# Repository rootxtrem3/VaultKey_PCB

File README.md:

# VaultKey USB

> **This README is also generated by an AI agent cuz why not. All those PCB designing that i ain't used to and coding are enough for me!**

VaultKey USB is a compact ESP32-S3 hardware-key PCB with a native USB-A edge
connector, 128x64 OLED, four navigation buttons, a recessed reset switch, and a CR2032-backed DS1307 real-time
clock. This project targets **KiCad 10** and includes the routed PCB, matching
schematic, project rules, manufacturing data, assembly data, reports, STEP
model, and documentation plots.

## Validation status

The release artifacts in this directory were generated with KiCad 10.0.8.

| Check | Result |
|---|---:|
| PCB DRC | **0 violations, 0 unconnected pads** |
| PCB pad connectivity | **0 unconnected pads after GND stitching via** |
| Schematic ERC | **0 violations** |
| Schematic-to-PCB comparison | **105 connected pins, 0 mismatches** |
| Board outline | **112.500 x 50.000 mm** |
| Copper layers / thickness | **2 / 1.600 mm** |
| USB D+/D- routed-length mismatch | **6.625 mm** |
| USB-A PCB-edge pad order/geometry | **PASS** |

Rev E adds TP1 BOOT-to-GND recovery pads and MCU GPIO1 control of the green
status LED. Existing component placement and board outline are unchanged. The
current PCB passes DRC after copper-zone refill. Gerbers, drill files, and
fabrication archives are regenerated from this board. Validate the assembled
hardware before production use.

The machine-generated reports are under `fabrication/reports/`.
Cosmetic silkscreen-to-copper, silkscreen-overlap, and silkscreen-edge checks
are intentionally set to ignore in the project rules; electrical, clearance,
hole, courtyard, connectivity, and copper-edge checks remain enabled.

## Mechanical definition

- Overall coordinate bounds: `X=0..112.5 mm`, `Y=0..50.0 mm`.
- Main body: `X=12.0..112.5 mm`, **100.5 x 50.0 mm**.
- USB-A tongue: `X=0..12.0 mm`, `Y=19.0..31.0 mm`, with 0.5 mm 45-degree
  tip chamfers.
- Four 2.7 mm NPTH mounting holes:
  - H1 `(16.0, 3.5)`
  - H2 `(15.0, 47.0)`
  - H3 `(108.5, 3.5)`
  - H4 `(108.0, 46.0)`
- Two-layer, 1.6 mm FR4. All vias are tented on both sides.
- Contact finish: standard ENIG; hard-gold edge plating is not specified for
  this low-cycle prototype. Confirm insertion-cycle requirements with the
  fabricator and USB host connector.
- Front and rear silkscreens include component references; controls and major
  blocks also carry functional labels for assembly and use.

The required USB, display, module, RTC, and four D-pad placements remain at
their locked source coordinates. See
`fabrication/reports/mechanical_validation.txt` for the exact check output.

## Circuit overview

### Power and USB

- USB VBUS passes through F1, a 0.5 A resettable fuse, to the `+5V` rail.
- U3 (AMS1117-3.3) produces `+3V3` with 10 uF input and 22 uF output bulk
  capacitance.
- U5 (USBLC6-2SC6, bottom side) protects USB D+, D-, and VBUS from ESD.
- C9 provides local post-fuse USB input bypassing.
- D1 is an active-high MCU status LED driven by GPIO1 through R5 (1 kΩ).
- J1 is a true front-copper PCB-edge USB-A plug. The four contacts lie on the
  `X=0..12 mm` tongue. With the insertion tip facing left, top-to-bottom order
  is GND, D+, D-, VBUS. The connector pads run toward the body in +X. VBUS/GND are
  7.0 mm long; D-/D+ are recessed to 6.0 mm for make-first/break-last mating.
- Copper-zone fill and silkscreen are excluded from the complete mating tongue.

### Controller and controls

- U1 is an ESP32-S3-WROOM-1U module; connect an appropriate external 2.4 GHz
  antenna to its RF connector.
- Native USB uses module pins USB_D- and USB_D+.
- R6 (10k) pulls EN high and C7 (100nF) provides the RC delay, so the module
  leaves reset automatically when USB power is applied.
- SW5 is a small SMD tactile switch from EN to GND, recessed under a pinhole in
  the enclosure and operated with a needle or SIM-ejector tool. It is not a
  finger-operated reset button.
- R7 (10k) holds GPIO0 high for normal flash boot. TP1.1 is BOOT and TP1.2 is
  GND; bridge them while pulsing SW5/EN to enter ROM recovery mode. Remove the
  bridge after the ROM USB device appears. Validate this sequence on hardware.
- Enclosure reset access: SW5 sits on the front side at (104.0, 13.5) mm. Put a
  1.0-1.2 mm pinhole in the lid directly above that point; the switch body is
  4.2 x 3.2 mm and 2.5 mm tall, so it is not reachable by a finger. Press it
  with a needle or SIM-ejector tool. The pinhole is clear of H3/H4, the OLED,
  the four user buttons, the USB tongue and the ESP32 antenna.

Firmware-facing control assignment:

| Function | ESP32-S3 signal |
|---|---|
| Select | GPIO4 |
| Down | GPIO5 |
| Back | GPIO6 |
| Up | GPIO7 |
| OLED SDA | GPIO8 |
| OLED SCL | GPIO9 |
| OLED reset | GPIO13 |
| Boot | GPIO0 |
| Status LED | GPIO1 |

### OLED and RTC

- DS1 is the Adafruit 1.3-inch SSD1306 128x64 breakout footprint. Configure
  the module for I2C operation.
- OLED pin 7 (VIN) uses +5 V, pins 3 (DC/SA0) and 5 (CS) are strapped low,
  and pin 6 (the breakout's 3.3 V output) is intentionally unconnected.
- U2 is a 5 V DS1307+ with a 32.768 kHz crystal and bottom-side CR2032 backup.
- U4 (PCA9306) translates between the 3.3 V ESP32/OLED bus and the 5 V RTC
  bus. Both sides have 4.7 kOhm pull-ups.
- PCA9306 pins VREF2 and EN share `I2C_BIAS`; R8 (200 kOhm) biases that node
  from +5 V and C5 (100 pF) filters it, following the TI reference circuit.

## Important assembly notes

1. **Battery polarity:** BT1 is a bottom-side Keystone 1058/1058TR low-profile
   slot-style holder. Pad 1 is `VBAT` (+) and pad 2 is GND (-); confirm the
   procured holder's marking before inserting a cell.
2. **OLED mounting:** the OLED is installed on its 8-pin header. The four
   OLED-module corner drills have intentionally been removed from the carrier
   PCB; only the four main-board mounting holes remain.
3. **USB current/thermal margin:** validate worst-case ESP32 radio current,
   polyfuse behavior, AMS1117 dissipation, and enclosure temperature in the
   final product. The 0.5 A input fuse is deliberately conservative.
4. The project-local U1 STEP file is an **assembly-envelope model**, not
   vendor-controlled mechanical CAD. Its U.FL connector end matches the KiCad
   footprint, but do not use the model to machine mating parts.
5. The locked stackup is 1.6 mm FR4. Confirm mechanical retention and contact
   wear with the intended USB-A receptacle before production.

## Project structure

| Path | Contents |
|---|---|
| `VaultKey_USB.kicad_pro` | KiCad project and DRC/ERC settings |
| `VaultKey_USB.kicad_sch` | Complete matching schematic |
| `VaultKey_USB.kicad_pcb` | Fully routed two-layer PCB |
| `lib/VaultKey.pretty/` | Custom USB edge, NPTH, and hole-free OLED footprints |
| `lib/VaultKey.3dshapes/` | Project-local ESP32 assembly-envelope STEP model |
| `fabrication/gerbers/` | X2 Gerbers for copper, mask, paste, silk, and outline |
| `fabrication/drill/` | Separate plated/NPTH Excellon and drill maps |
| `fabrication/assembly/` | BOM and component-position CSV files |
| `fabrication/reports/` | DRC, ERC, netlist, IPC-D-356, drill, and statistics reports |
| `fabrication/3d/` | Complete board STEP export |
| `docs/` | Schematic PDF, 1:1 PCB plots, SVGs, and 3D renders |
| `generator/` | Deterministic source data and validation/export scripts |

The regenerated package is available at:
`fabrication/VaultKey_USB_Gerbers_and_Drill.zip`. Verify its contents against
your fabricator's layer naming and stackup requirements before ordering.
`fabrication/VaultKey_USB_Manufacturing_Package.zip` additionally contains the
BOM, placement files, reports, IPC-D-356 data, STEP model, and this README.

## Open and export

Open `VaultKey_USB.kicad_pro` in KiCad 10. To reproduce all validation and
release artifacts:

```bash
cd /home/rootx/Projects/VaultKey_USB
python3 generator/export_fabrication.py
```

This requires `kicad-cli`, the KiCad `pcbnew` Python module, and `FreeCADCmd`
for the two project-local envelope models.

The final PCB is already routed. `generator/build_pcb.py` intentionally
recreates an **unrouted** board and overwrites `VaultKey_USB.kicad_pcb`; use it
only when starting a new routing pass. The `.dsn`/`.ses` files in
`fabrication/` are retained as initial FreeRouting history and are not the
authoritative final board after the documented post-route corrections.

## Manufacturing constraints

- Minimum track width: 0.20 mm
- Minimum clearance: 0.20 mm
- Minimum copper-to-edge: 0.50 mm
- Hole clearance: 0.25 mm
- Hole-to-hole minimum: 0.25 mm
- Standard via: 0.60/0.30 mm
- Power via: 0.80/0.40 mm

See `fabrication/MANUFACTURING_NOTES.txt` for the concise release notes sent
with the Gerber archive.
Detailed USB pad measurements and connectivity checks are recorded in
`fabrication/reports/USB_contact_verification.txt`.

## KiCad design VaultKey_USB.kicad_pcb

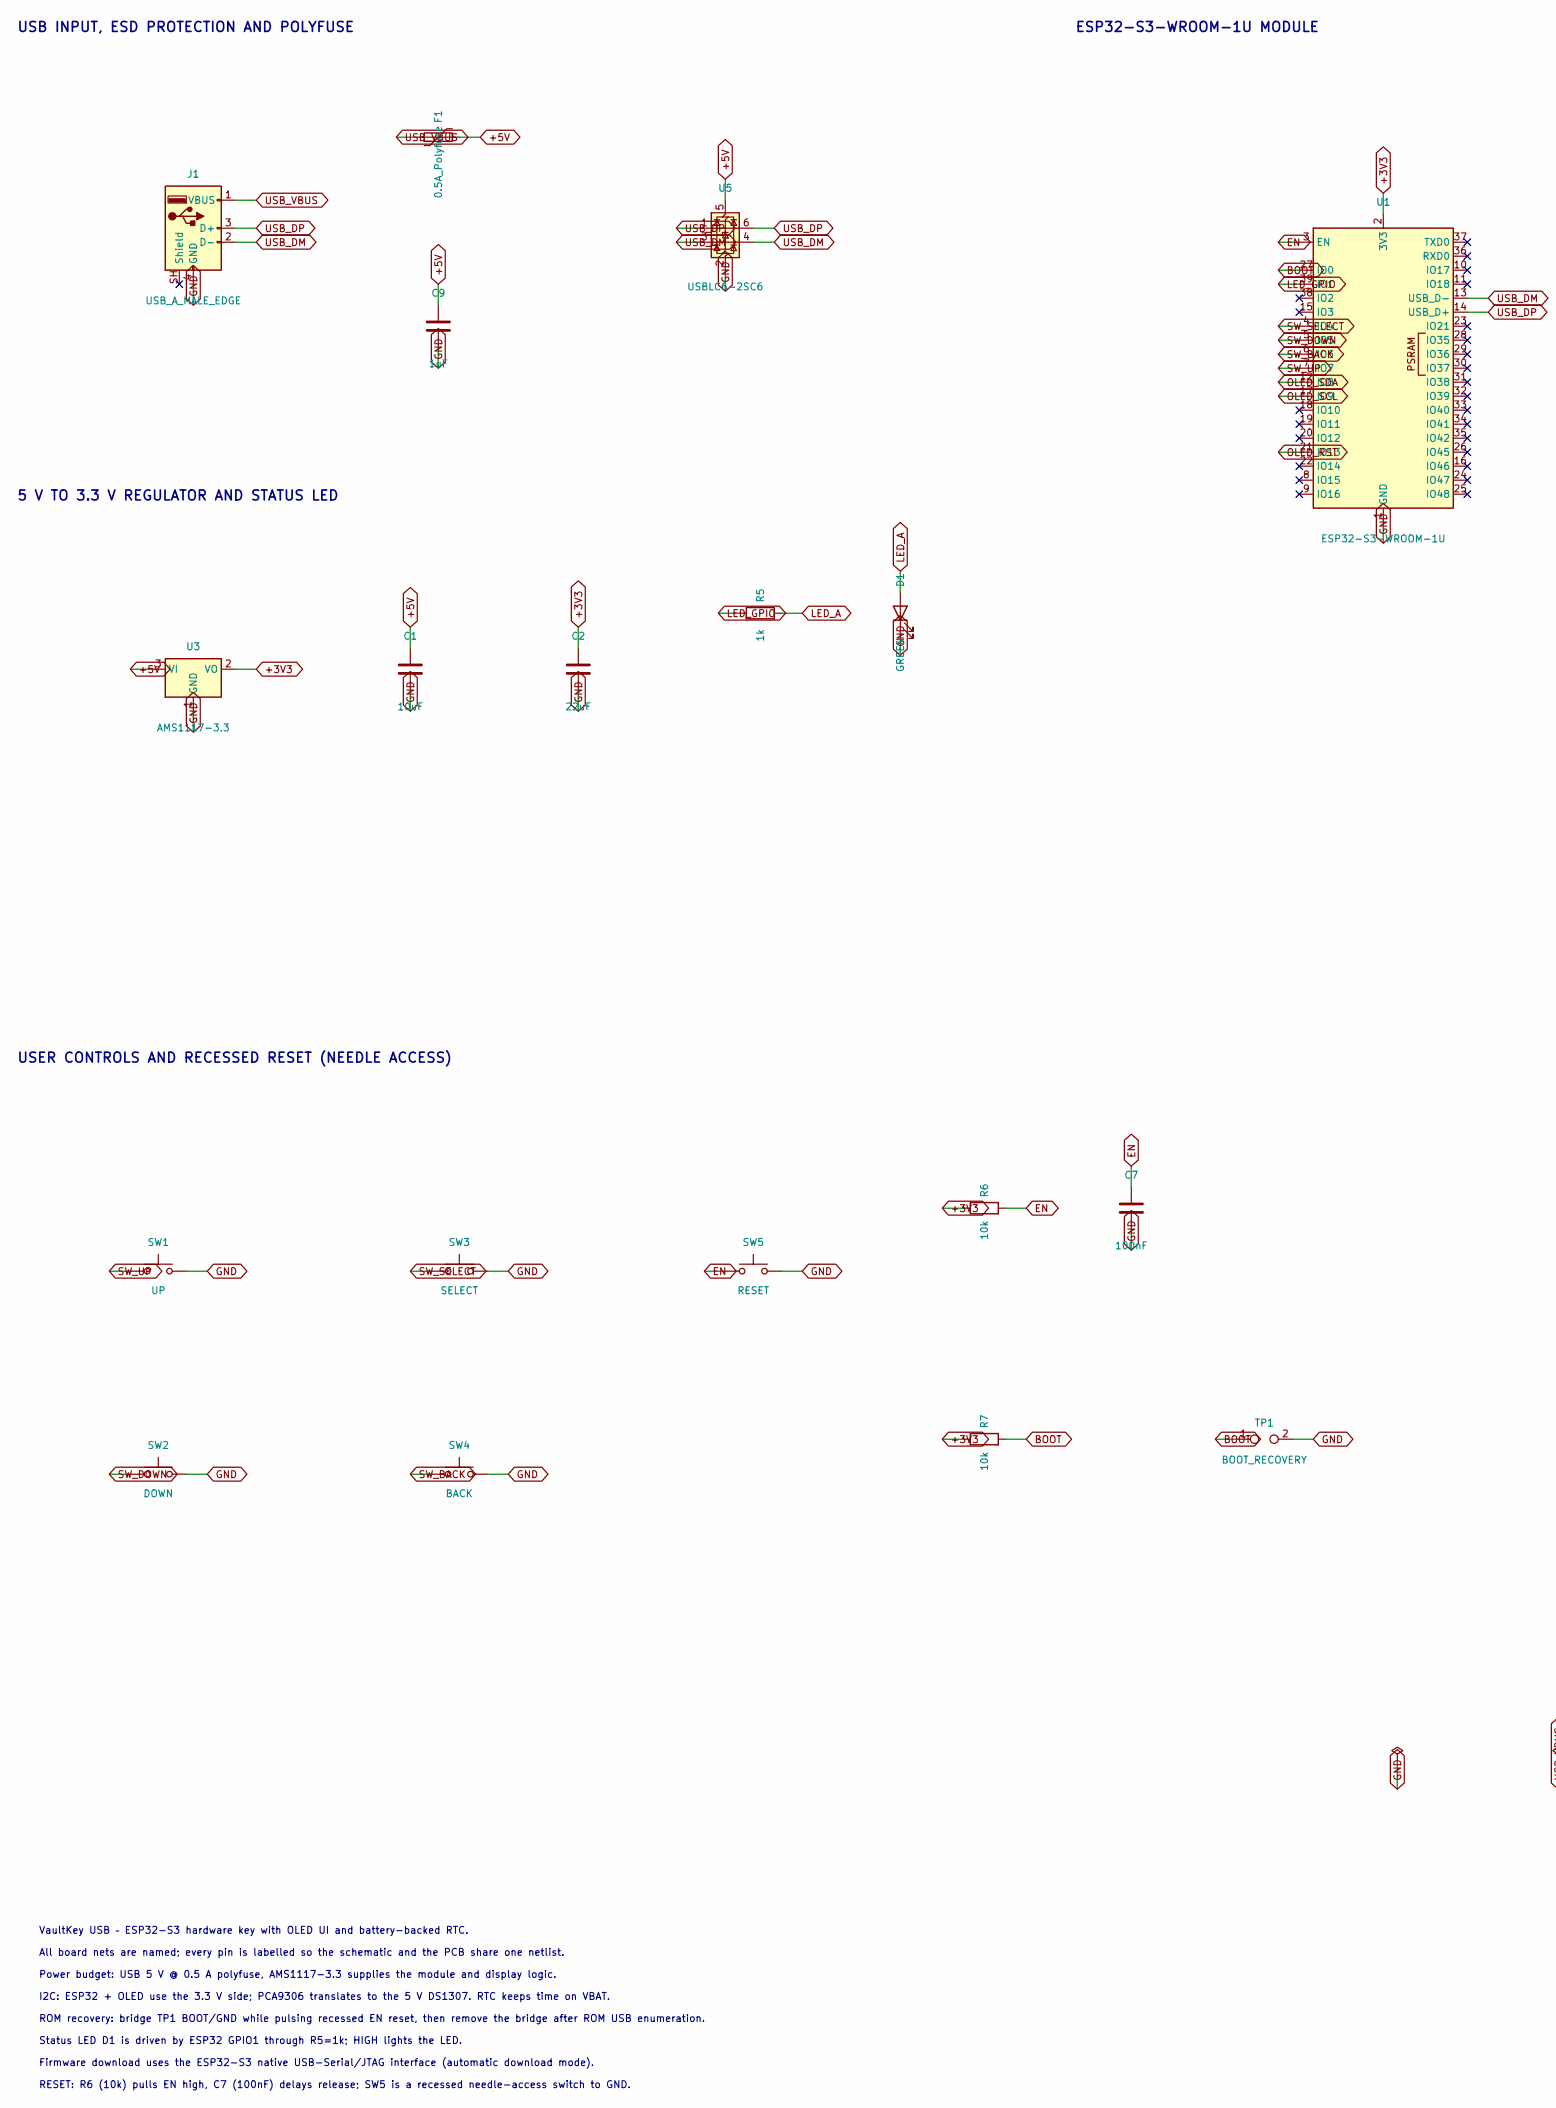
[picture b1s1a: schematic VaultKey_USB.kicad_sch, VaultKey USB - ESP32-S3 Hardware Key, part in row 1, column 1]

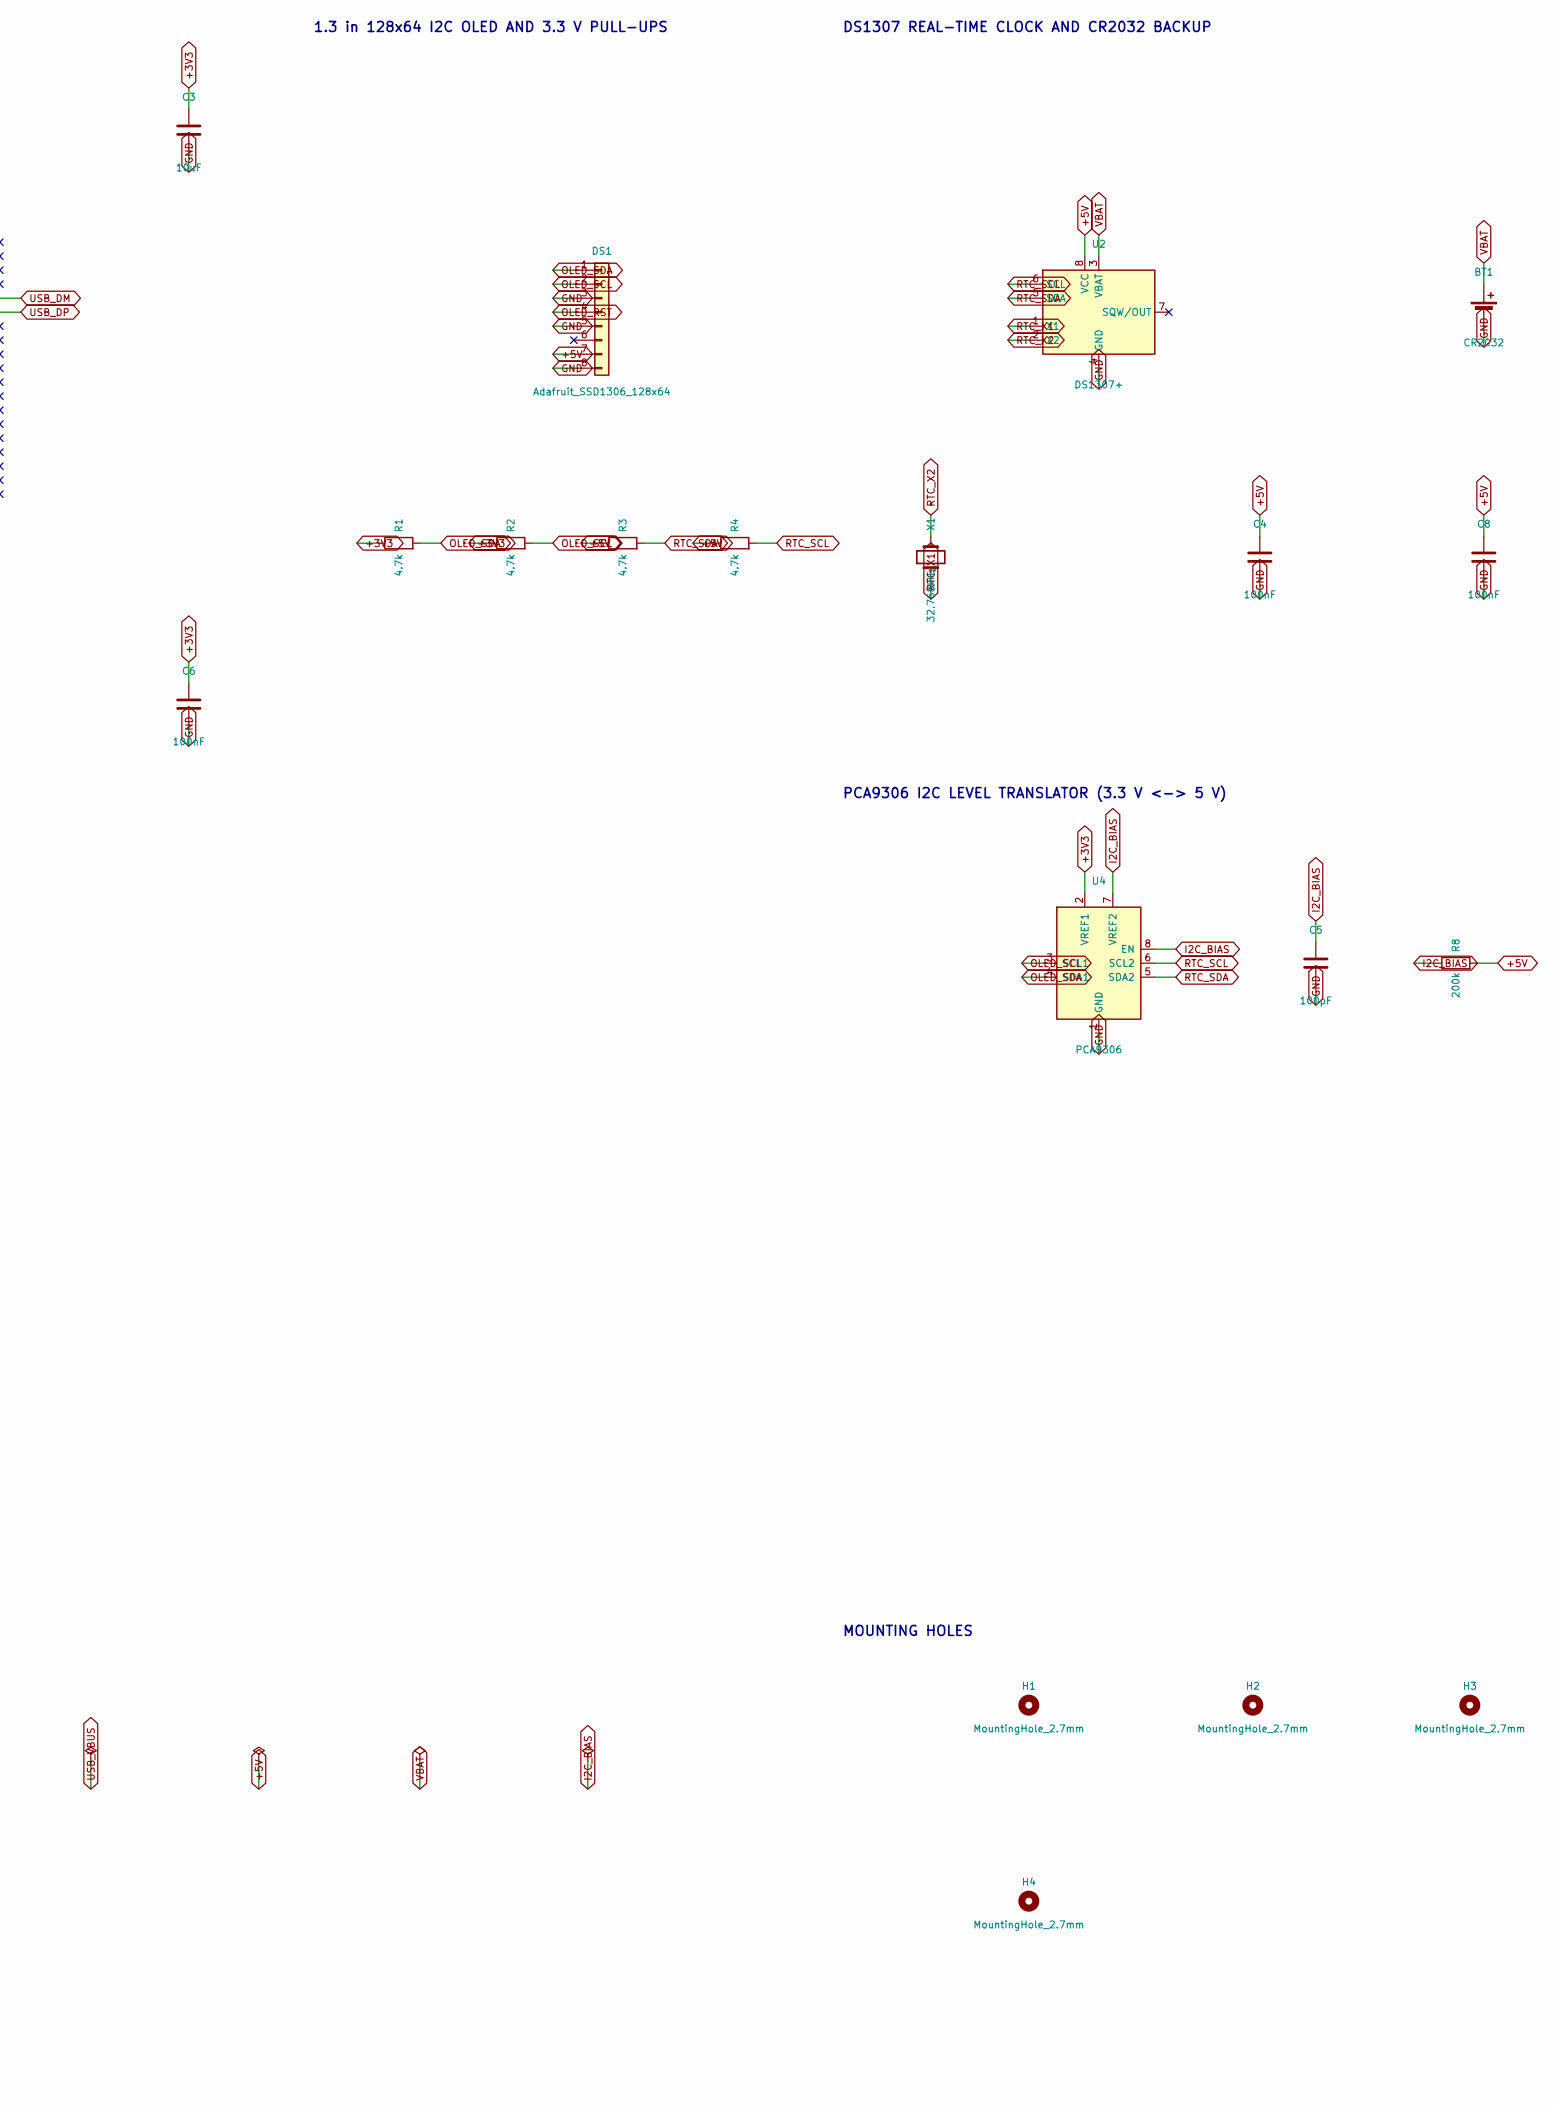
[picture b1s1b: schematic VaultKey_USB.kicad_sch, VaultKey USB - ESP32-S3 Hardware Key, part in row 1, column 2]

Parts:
BT1: CR2032; BatteryHolder_Keystone_1058_1x2032
C1, C3: 10uF; C_1206_3216Metric
C2: 22uF; C_1206_3216Metric
C4, C6, C7, C8: 100nF; C_0805_2012Metric
C5: 100pF; C_0805_2012Metric
C9: 1uF; C_0805_2012Metric
D1: GREEN; LED_0805_2012Metric
DS1: Adafruit_SSD1306_128x64; Adafruit_SSD1306_NoMountingHoles
F1: 0.5A_Polyfuse; Fuse_1206_3216Metric
H1, H2, H3, H4: MountingHole_2.7mm; MountingHole_2.7mm_NPTH_Custom
J1: USB_A_MALE_EDGE; VaultKey_USB_A_Male_PCB_Edge
R1, R2, R3, R4: 4.7k; R_0805_2012Metric
R5: 1k; R_0805_2012Metric
R6, R7: 10k; R_0805_2012Metric
R8: 200k; R_0805_2012Metric
SW1: UP; SW_Push_1TS009xxxx-xxxx-xxxx_6x6x5mm
SW2: DOWN; SW_Push_1TS009xxxx-xxxx-xxxx_6x6x5mm
SW3: SELECT; SW_Push_1TS009xxxx-xxxx-xxxx_6x6x5mm
SW4: BACK; SW_Push_1TS009xxxx-xxxx-xxxx_6x6x5mm
SW5: RESET; SW_Push_1P1T_NO_Vertical_Wuerth_434133025816
TP1: BOOT_RECOVERY; TestPoint_2Pads_Pitch2.54mm_Drill0.8mm
U1: ESP32-S3-WROOM-1U
U2: DS1307+; DIP-8_W7.62mm
U3: AMS1117-3.3; SOT-223-3_TabPin2
U4: PCA9306; TSSOP-8_3x3mm_P0.65mm
U5: USBLC6-2SC6; SOT-23-6
X1: 32.768kHz; Crystal_SMD_3215-2Pin_3.2x1.5mm

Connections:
+3V3: C2.1, C3.1, C6.1, R1.1, R2.1, R6.1, R7.1, U1.2 (3V3), U3.2 (VO), U4.2 (VREF1)
+5V: C1.1, C4.1, C8.1, C9.1, DS1.7, F1.2, R3.1, R4.1, R8.2, U2.8 (VCC), U3.3 (VI), U5.5 (VBUS)
BOOT: R7.2, TP1.1, U1.27 (IO0)
EN: C7.1, R6.2, SW5.1, U1.3 (EN)
GND: BT1.2 (-), C1.2, C2.2, C3.2, C4.2, C5.2, C6.2, C7.2, C8.2, C9.2, D1.1 (K), DS1.3, DS1.5, DS1.8, J1.4 (VBUS_1), SW1.2, SW2.2, SW3.2, SW4.2, SW5.2, TP1.2, U1.1 (GND), U1.40 (GND), U1.41 (GND), U2.4 (GND), U3.1 (GND), U4.1 (GND), U5.2 (GND)
I2C_BIAS: C5.1, R8.1, U4.7 (VREF2), U4.8 (EN)
LED_A: D1.2 (A), R5.2
LED_GPIO: R5.1, U1.39 (IO1)
OLED_RST: DS1.4, U1.21 (IO13)
OLED_SCL: DS1.2, R2.2, U1.17 (IO9), U4.3 (SCL1)
OLED_SDA: DS1.1, R1.2, U1.12 (IO8), U4.4 (SDA1)
RTC_SCL: R4.2, U2.6 (SCL), U4.6 (SCL2)
RTC_SDA: R3.2, U2.5 (SDA), U4.5 (SDA2)
RTC_X1: U2.1 (X1), X1.1
RTC_X2: U2.2 (X2), X1.2
SW_BACK: SW4.1, U1.6 (IO6)
SW_DOWN: SW2.1, U1.5 (IO5)
SW_SELECT: SW3.1, U1.4 (IO4)
SW_UP: SW1.1, U1.7 (IO7)
USB_DM: J1.2 (D+_3), U1.13 (USB_D-), U5.3 (I/O2), U5.4 (I/O2)
USB_DP: J1.3 (D-_2), U1.14 (USB_D+), U5.1 (I/O1), U5.6 (I/O1)
USB_VBUS: F1.1, J1.1 (GND_4)
VBAT: BT1.1 (+), U2.3 (VBAT)

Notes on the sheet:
USB INPUT, ESD PROTECTION AND POLYFUSE
5 V TO 3.3 V REGULATOR AND STATUS LED
ESP32-S3-WROOM-1U MODULE
1.3 in 128x64 I2C OLED AND 3.3 V PULL-UPS
DS1307 REAL-TIME CLOCK AND CR2032 BACKUP
PCA9306 I2C LEVEL TRANSLATOR (3.3 V <-> 5 V)
USER CONTROLS AND RECESSED RESET (NEEDLE ACCESS)
MOUNTING HOLES
VaultKey USB – ESP32-S3 hardware key with OLED UI and battery-backed RTC.
All board nets are named; every pin is labelled so the schematic and the PCB share one netlist.
Power budget: USB 5 V @ 0.5 A polyfuse, AMS1117-3.3 supplies the module and display logic.
I2C: ESP32 + OLED use the 3.3 V side; PCA9306 translates to the 5 V DS1307. RTC keeps time on VBAT.
ROM recovery: bridge TP1 BOOT/GND while pulsing recessed EN reset, then remove the bridge after ROM USB enumeration.
Status LED D1 is driven by ESP32 GPIO1 through R5=1k; HIGH lights the LED.
Firmware download uses the ESP32-S3 native USB-Serial/JTAG interface (automatic download mode).
RESET: R6 (10k) pulls EN high, C7 (100nF) delays release; SW5 is a recessed needle-access switch to GND.

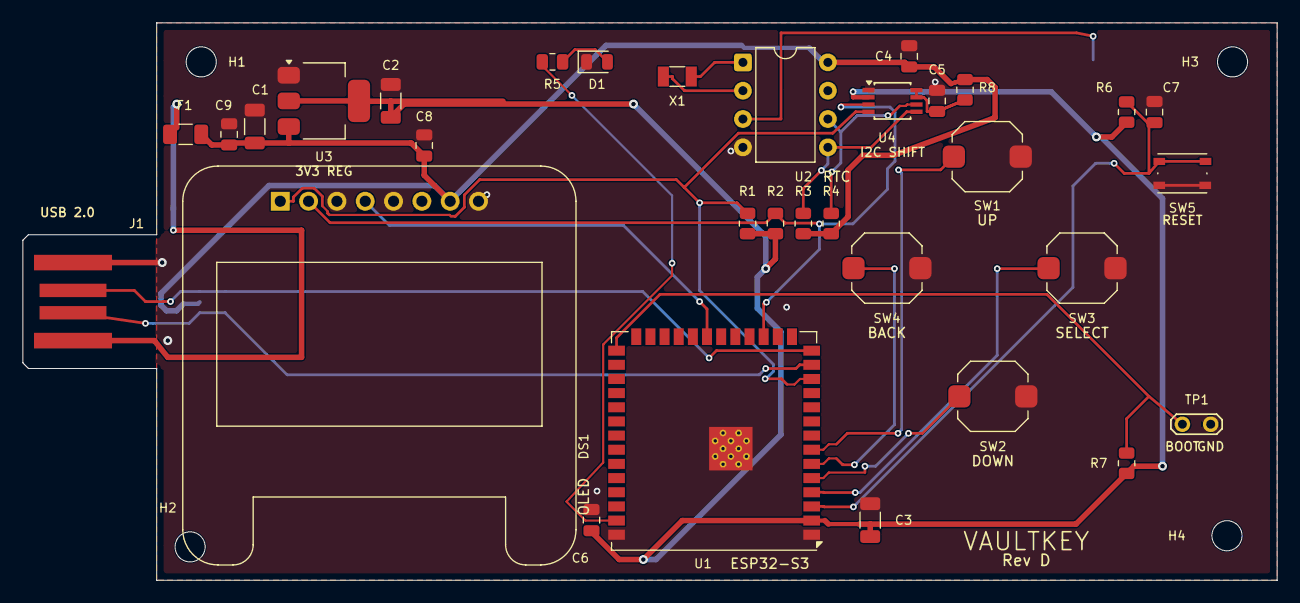
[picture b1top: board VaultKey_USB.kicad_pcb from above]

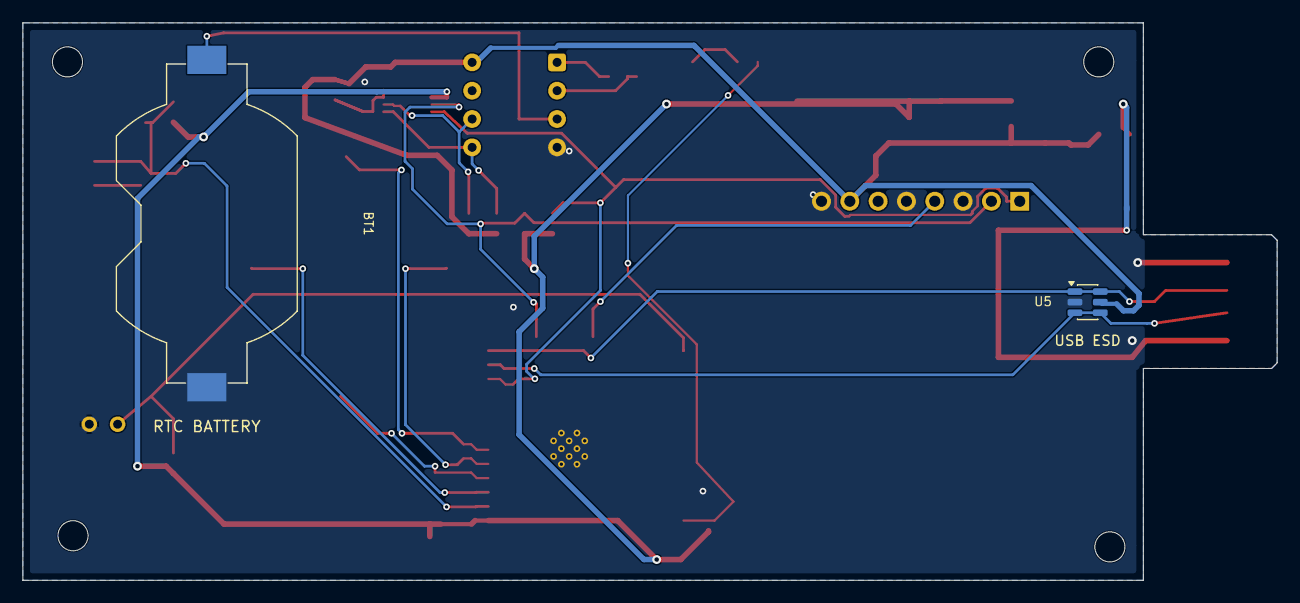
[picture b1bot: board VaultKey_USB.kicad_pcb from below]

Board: 2 copper layers, 112.5 x 50.0 mm, 38 parts (2 on the bottom side), 23 nets.

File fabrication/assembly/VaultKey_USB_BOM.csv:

"References","Value","Footprint","Description","Quantity","DNP"
"BT1","CR2032","Battery:BatteryHolder_Keystone_1058_1x2032","Keystone 1058 low-profile slot-style CR2032 holder","1",""
"C1,C3","10uF","Capacitor_SMD:C_1206_3216Metric","ESP32 bulk decoupling,Regulator input capacitor","2",""
"C2","22uF","Capacitor_SMD:C_1206_3216Metric","Regulator output capacitor","1",""
"C4,C6-C8","100nF","Capacitor_SMD:C_0805_2012Metric","DS1307 VCC bypass,EN RC delay capacitor,ESP32 local decoupling,OLED VIN bypass","4",""
"C5","100pF","Capacitor_SMD:C_0805_2012Metric","PCA9306 VREF2/EN filter capacitor","1",""
"C9","1uF","Capacitor_SMD:C_0805_2012Metric","USB VBUS input bypass","1",""
"D1","GREEN","LED_SMD:LED_0805_2012Metric","GPIO-controlled green status LED (pad 1 cathode)","1",""
"DS1","Adafruit_SSD1306_128x64","VaultKey:Adafruit_SSD1306_NoMountingHoles","Adafruit 1.3 inch 128x64 I2C OLED breakout","1",""
"F1","0.5A_Polyfuse","Fuse:Fuse_1206_3216Metric","Resettable 0.5 A USB input fuse","1",""
"J1","USB_A_MALE_EDGE","VaultKey:VaultKey_USB_A_Male_PCB_Edge","USB 2.0 Type-A male edge connector","1",""
"R1-R4","4.7k","Resistor_SMD:R_0805_2012Metric","3.3 V SCL pull-up,3.3 V SDA pull-up,5 V SCL pull-up,5 V SDA pull-up","4",""
"R5","1k","Resistor_SMD:R_0805_2012Metric","Status LED current limiter","1",""
"R6,R7","10k","Resistor_SMD:R_0805_2012Metric","BOOT/GPIO0 pull-up,EN pull-up","2",""
"R8","200k","Resistor_SMD:R_0805_2012Metric","PCA9306 VREF2/EN bias resistor (TI recommended)","1",""
"SW1","UP","Button_Switch_SMD:SW_Push_1TS009xxxx-xxxx-xxxx_6x6x5mm","Navigation up","1",""
"SW2","DOWN","Button_Switch_SMD:SW_Push_1TS009xxxx-xxxx-xxxx_6x6x5mm","Navigation down","1",""
"SW3","SELECT","Button_Switch_SMD:SW_Push_1TS009xxxx-xxxx-xxxx_6x6x5mm","Navigation select","1",""
"SW4","BACK","Button_Switch_SMD:SW_Push_1TS009xxxx-xxxx-xxxx_6x6x5mm","Navigation back","1",""
"SW5","RESET","Button_Switch_SMD:SW_Push_1P1T_NO_Vertical_Wuerth_434133025816","Recessed EN/reset switch, needle access only","1",""
"TP1","BOOT_RECOVERY","TestPoint:TestPoint_2Pads_Pitch2.54mm_Drill0.8mm","Bridge BOOT to GND during reset for ROM recovery","1",""
"U1","ESP32-S3-WROOM-1U","RF_Module:ESP32-S3-WROOM-1U","ESP32-S3 Wi-Fi/BLE module with external antenna","1",""
"U2","DS1307+","Package_DIP:DIP-8_W7.62mm","I2C real-time clock","1",""
"U3","AMS1117-3.3","Package_TO_SOT_SMD:SOT-223-3_TabPin2","1 A low-dropout 3.3 V regulator","1",""
"U4","PCA9306","Package_SO:TSSOP-8_3x3mm_P0.65mm","Bidirectional I2C level translator, 3.3 V to 5 V","1",""
"U5","USBLC6-2SC6","Package_TO_SOT_SMD:SOT-23-6","USB ESD protection array","1",""
"X1","32.768kHz","Crystal:Crystal_SMD_3215-2Pin_3.2x1.5mm","RTC crystal","1",""
